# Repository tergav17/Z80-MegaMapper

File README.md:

# Z80 MegaMapper

The Z80 MegaMapper (ZMM) is designed to enhance the ability of existing retro computers. This is done by interposing the Z80 CPU and intercepting certain signals. The current version of the MegaMapper provides the following enhancements:

- An additional 512 KB of static RAM, expandable up to 2 MB.
- Simple memory management, allowing the 4 independently selectable memory banks. Banks can also be write protected.
- Virtual machine mode, supporting “transparent” traps that do not depend on a specific stack pointer location.
- Fully programmable I/O space in virtual mode, allowing device addresses to be translated between the virtual and physical address space.
- I/O trap vector allowing any I/O instruction to be emulated by software if needed.
- Software controllable interrupts, allowing the maskable interrupt to be fully controlled by the real mode hypervisor.

The expanded memory is fairly self explanatory, but the other features may require a bit of explanation. The goal of the MegaMapper is to allow a Z80 machine to support “virtual machines”. These machines, with the help of a software hypervisor, can be made to seamlessly run software from other computer architectures. A single machine can act as an MSX, Colecovision, SG-1000, ZX81, Heathkit H8, TRS-80 Model II, TI-83, etc… simply by changing what hypervisor software is running. Additionally, virtual machines can be debugged in real time, to the point of being single-steppable. 

This is different from emulation as fundamentally everything is still executing on bare hardware. It provides vast software compatibility while still scratching the “retro hardware” itch that makes emulators simply not as fun (personally). In theory, this same type of device could have been built in the 80s with off-the-shelf components. All of the heavy lifting is still done by the ~3.5 Mhz Z80 processor.

Admittedly, emulation can always provide better results than a janky virtualization set up like this. This is more of a “Because I Can” project than anything else. 

# Virtual Machine Status

## SG-1000

The important parts of this seem to work. The PSG -> AY translation is passable, but it still needs some work in terms of tone and support for the noise channel. Pausing is also buggy due to lack of functional NMI.

## MSX 1

Boots to MSX basic just fine. Can also run all of the 32K cartridge ROMs I threw at it. Keyboard matrix still needs to be updated to support all keys.

# Current Issues

The Z80 data bus buffer currently doesn't work properly due to IM2-related shenanigans. The system works fine without it, so it may be omitted in a future revision.

At the moment, there is no way to maintain IFF2 contents during a trap. This is fine for systems that don't need an NMI, but can cause interrupt issues to those that do. It should be possible to add a status bit that keeps trick of if IFF1 and IFF2 are supposed to be equal, and work backwards from there.

The classic NMOS CPUs seem to have issues sometimes with detecting clock edges on the M1 cycle. Currently, this is circumvented by just getting a faster CMOS Z80.

# Installation

The ZMM is designed to slot directly into where the Z80 plugs into the mainboard of the host computer. Everything runs on +5V, so no additional jumpers are needed.

# Limitations

One of the major design limitations of the ZMM is the fact that no provisions have been made for memory mapped I/O. Video RAM can crudely be accomplished by periodically scanning parts of memory and updating the VDP accordingly. This is very inefficient, especially the bigger the VRAM section gets. The size of the bankable sections is also limited to 16 KB, anything smaller will have to be emulated by manually copying sections of memory.

# BOM

| Quantity | Reference  | Part          | Link |
| -------- | ---------- | ------------- | ---- |
|        1 | U2         | 74LS32        |      |
|        2 | U3, U4     | 74LS670       |      |
|        1 | U5         | HM6116        |      |
|        3 | U6..8      | 74LS157       |      |
|        1 | U9         | 74LS244       |      |
|        2 | U10, U11   | 74LS374       |      |
|        1 | U12        | 74LS85        |      |
|        1 | U13        | XC9536PC44    |      |
|        1 | U14        | 74LS139       |      |
|      1-4 | U15..18    | AS6C4008      |      |
|        0 | U19        | 74LS245       |      |
|       19 | C1..19     | 0.1 uF C      |      |
|        1 | C20        | 100 uF        |      |

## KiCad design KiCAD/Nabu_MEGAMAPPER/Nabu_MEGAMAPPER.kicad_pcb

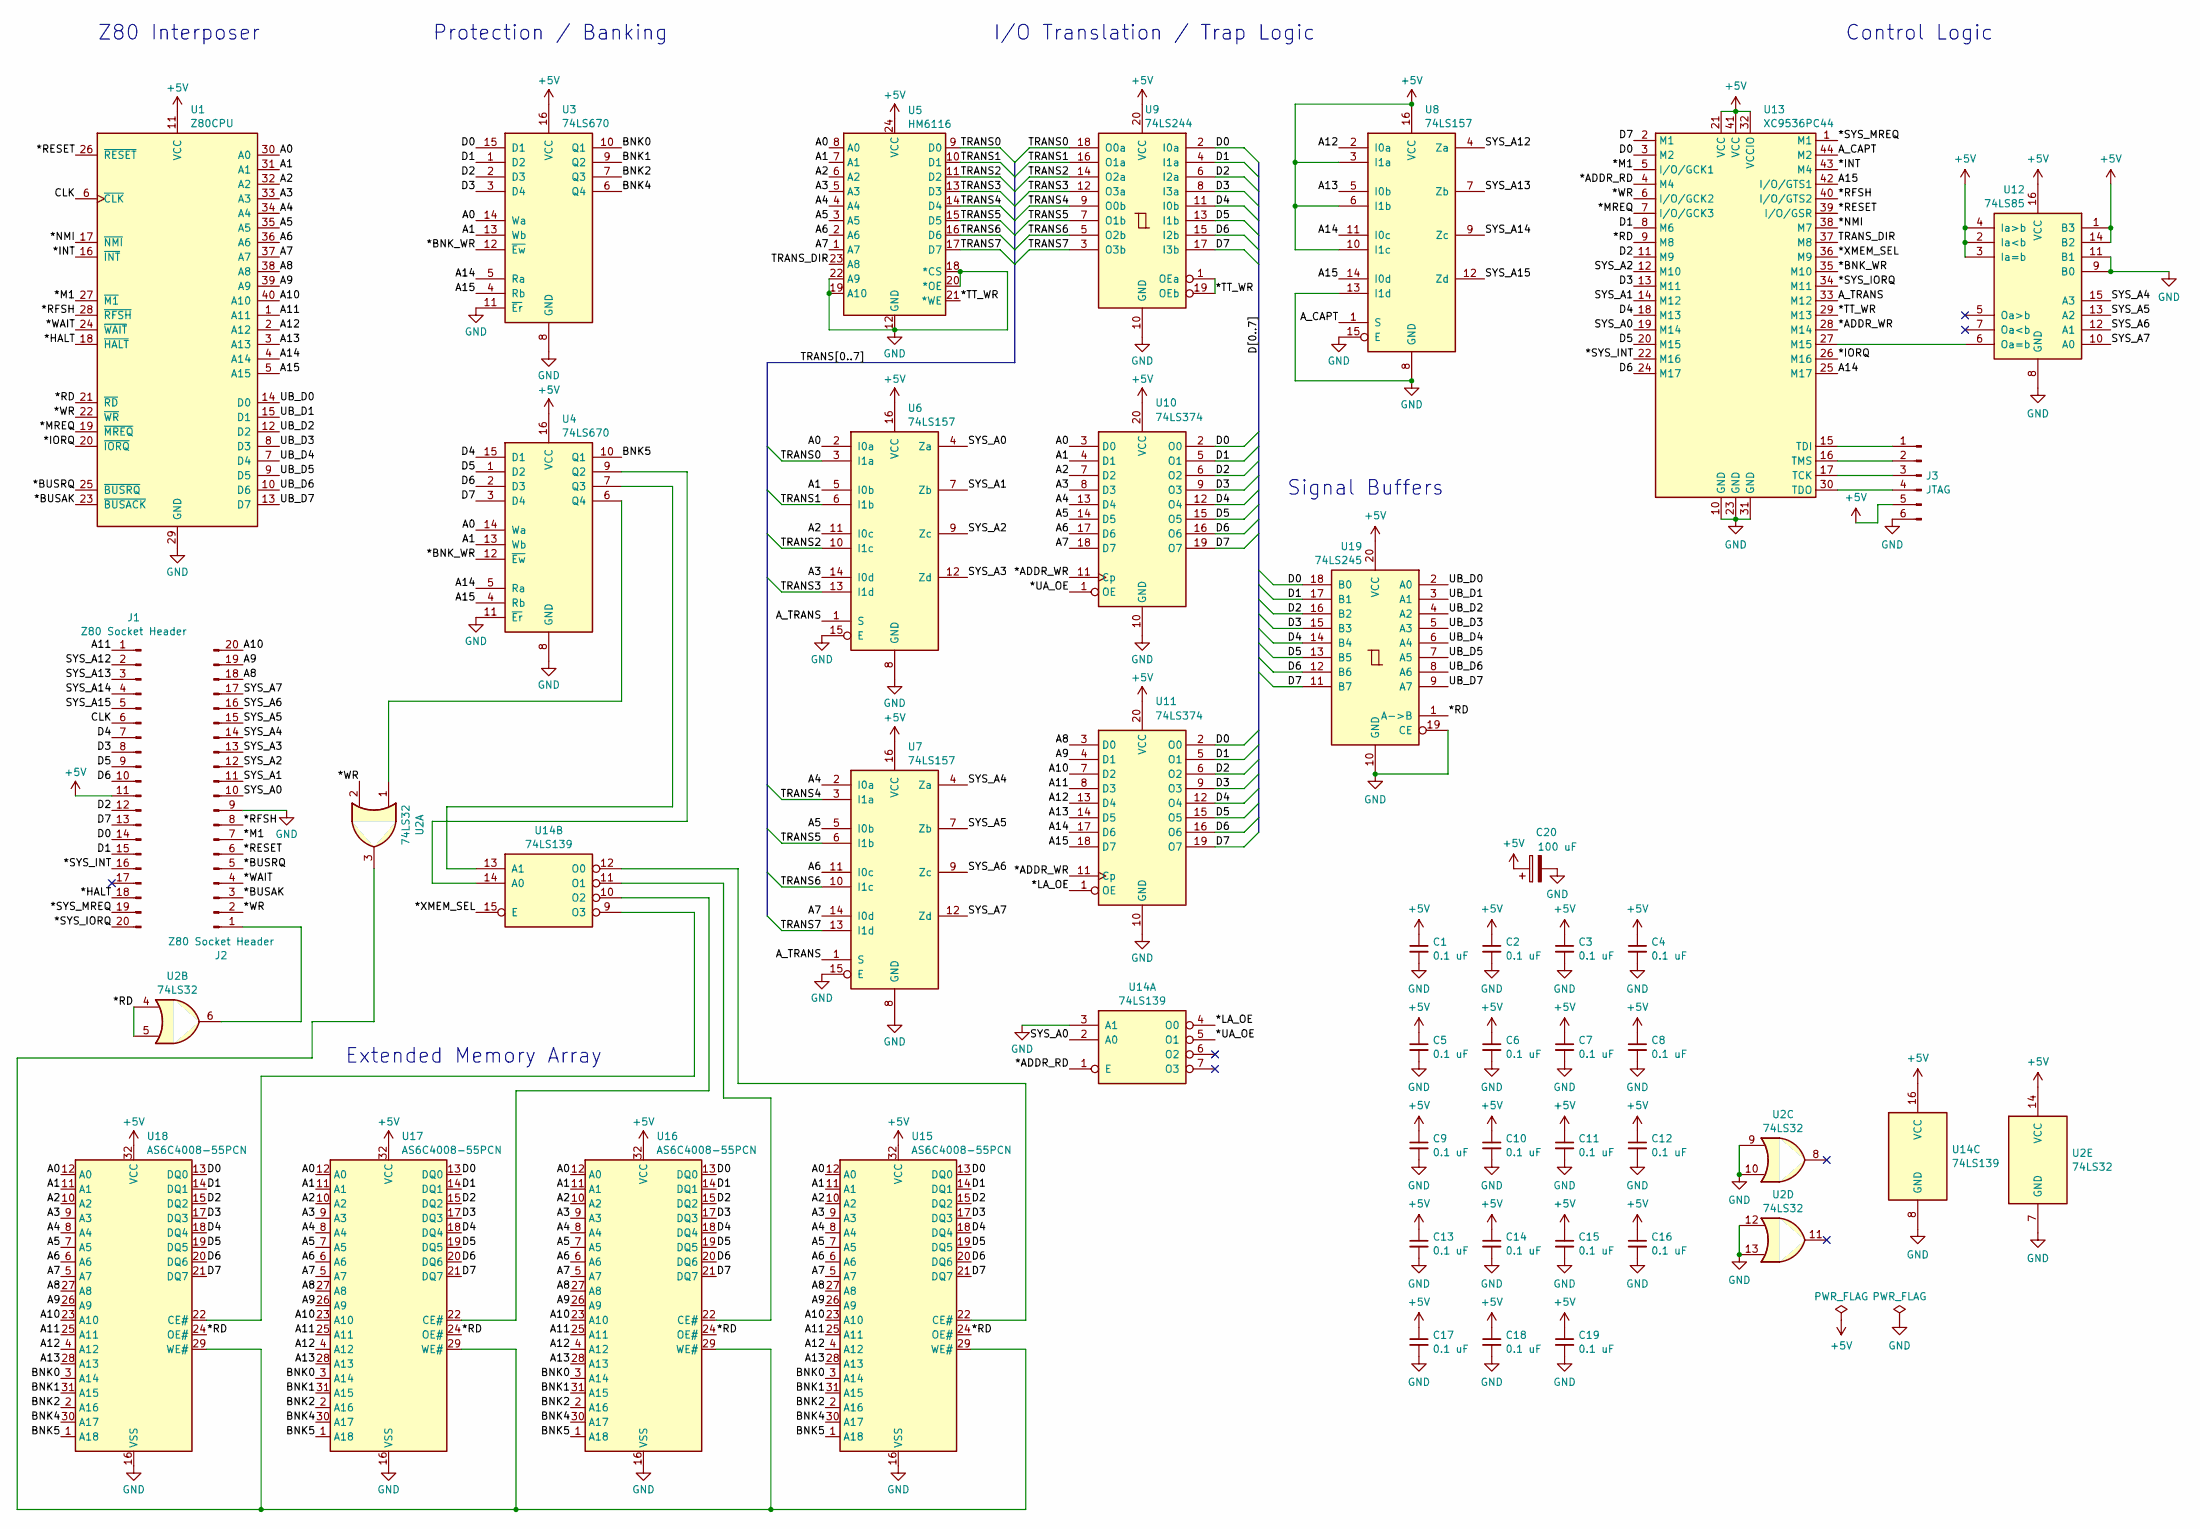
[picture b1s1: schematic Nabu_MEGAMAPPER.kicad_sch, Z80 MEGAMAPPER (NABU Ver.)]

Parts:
C1, C2, C3, C4, C5, C6, C7, C8, C9, C10, C11, C12, C13, C14, C15, C16, C17, C18, C19: 0.1 uF; C_Disc_D5.0mm_W2.5mm_P5.00mm
C20: 100 uF; CP_Radial_D6.3mm_P2.50mm
J1, J2: Z80 Socket Header; PinHeader_1x20_P2.54mm_Vertical
J3: JTAG; PinHeader_1x06_P2.54mm_Vertical
U1: Z80CPU; DIP-40_W15.24mm
U2: 74LS32; DIP-14_W7.62mm
U3, U4: 74LS670; DIP-16_W7.62mm
U5: HM6116; DIP-24_W15.24mm
U6, U7, U8: 74LS157; DIP-16_W7.62mm
U9: 74LS244; DIP-20_W7.62mm
U10, U11: 74LS374; DIP-20_W7.62mm
U12: 74LS85; DIP-16_W7.62mm
U13: XC9536PC44; PLCC-44_THT-Socket
U14: 74LS139; DIP-16_W7.62mm
U15, U16, U17, U18: AS6C4008-55PCN; DIP-32_W15.24mm
U19: 74LS245; DIP-20_W7.62mm

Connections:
+5V: C1.1, C2.1, C3.1, C4.1, C5.1, C6.1, C7.1, C8.1, C9.1, C10.1, C11.1, C12.1, C13.1, C14.1, C15.1, C16.1, C17.1, C18.1, C19.1, C20.1, J1.11, J3.5, U1.11 (VCC), U2.14 (VCC), U3.16 (VCC), U4.16 (VCC), U5.24 (VCC), U6.16 (VCC), U7.16 (VCC), U8.3 (I1a), U8.6 (I1b), U8.10 (I1c), U8.16 (VCC), U9.20 (VCC), U10.20 (VCC), U11.20 (VCC), U12.1 (B3), U12.2 (Ia<b), U12.3 (Ia=b), U12.4 (Ia>b), U12.14 (B2), U12.16 (VCC), U13.21 (VCC), U13.32 (VCCIO), U13.41 (VCC), U14.16 (VCC), U15.32 (VCC), U16.32 (VCC), U17.32 (VCC), U18.32 (VCC), U19.20 (VCC)
/*ADDR_RD: U13.4 (M4), U14.1 (E)
/*ADDR_WR: U10.11 (Cp), U11.11 (Cp), U13.28 (M14)
/*BNK_WR: U3.12 (~Ew), U4.12 (~Ew), U13.35 (M10)
/*BUSAK: J2.3, U1.23 (~BUSACK)
/*BUSRQ: J2.5, U1.25 (~BUSRQ)
/*HALT: J1.18, U1.18 (~HALT)
/*INT: U1.16 (~INT), U13.43 (M4)
/*IORQ: U1.20 (~IORQ), U13.26 (M16)
/*LA_OE: U11.1 (OE), U14.4 (O0)
/*M1: J2.7, U1.27 (~M1), U13.5 (I/O/GCK1)
/*MREQ: U1.19 (~MREQ), U13.7 (I/O/GCK3)
/*NMI: U1.17 (~NMI), U13.38 (M7)
/*RD: U1.21 (~RD), U2.4, U2.5, U13.9 (M8), U15.24 (OE#), U16.24 (OE#), U17.24 (OE#), U18.24 (OE#), U19.1 (A->B)
/*RESET: J2.6, U1.26 (~RESET), U13.39 (I/O/GSR)
/*RFSH: J2.8, U1.28 (~RFSH), U13.40 (I/O/GTS2)
/*SYS_INT: J1.16, U13.22 (M16)
/*SYS_IORQ: J1.20, U13.34 (M11)
/*SYS_MREQ: J1.19, U13.1 (M1)
/*TT_WR: U5.21 (*WE), U9.1 (OEa), U9.19 (OEb), U13.29 (M13)
/*UA_OE: U10.1 (OE), U14.5 (O1)
/*WAIT: J2.4, U1.24 (~WAIT)
/*WR: J2.2, U1.22 (~WR), U2.2, U13.6 (I/O/GCK2)
/*XMEM_SEL: U13.36 (M9), U14.15 (E)
/A0: U1.30 (A0), U3.14 (Wa), U4.14 (Wa), U5.8 (A0), U6.2 (I0a), U10.3 (D0), U15.12 (A0), U16.12 (A0), U17.12 (A0), U18.12 (A0)
/A1: U1.31 (A1), U3.13 (Wb), U4.13 (Wb), U5.7 (A1), U6.5 (I0b), U10.4 (D1), U15.11 (A1), U16.11 (A1), U17.11 (A1), U18.11 (A1)
/A2: U1.32 (A2), U5.6 (A2), U6.11 (I0c), U10.7 (D2), U15.10 (A2), U16.10 (A2), U17.10 (A2), U18.10 (A2)
/A3: U1.33 (A3), U5.5 (A3), U6.14 (I0d), U10.8 (D3), U15.9 (A3), U16.9 (A3), U17.9 (A3), U18.9 (A3)
/A4: U1.34 (A4), U5.4 (A4), U7.2 (I0a), U10.13 (D4), U15.8 (A4), U16.8 (A4), U17.8 (A4), U18.8 (A4)
/A5: U1.35 (A5), U5.3 (A5), U7.5 (I0b), U10.14 (D5), U15.7 (A5), U16.7 (A5), U17.7 (A5), U18.7 (A5)
/A6: U1.36 (A6), U5.2 (A6), U7.11 (I0c), U10.17 (D6), U15.6 (A6), U16.6 (A6), U17.6 (A6), U18.6 (A6)
/A7: U1.37 (A7), U5.1 (A7), U7.14 (I0d), U10.18 (D7), U15.5 (A7), U16.5 (A7), U17.5 (A7), U18.5 (A7)
/A8: J2.18, U1.38 (A8), U11.3 (D0), U15.27 (A8), U16.27 (A8), U17.27 (A8), U18.27 (A8)
/A9: J2.19, U1.39 (A9), U11.4 (D1), U15.26 (A9), U16.26 (A9), U17.26 (A9), U18.26 (A9)
/A10: J2.20, U1.40 (A10), U11.7 (D2), U15.23 (A10), U16.23 (A10), U17.23 (A10), U18.23 (A10)
/A11: J1.1, U1.1 (A11), U11.8 (D3), U15.25 (A11), U16.25 (A11), U17.25 (A11), U18.25 (A11)
/A12: U1.2 (A12), U8.2 (I0a), U11.13 (D4), U15.4 (A12), U16.4 (A12), U17.4 (A12), U18.4 (A12)
/A13: U1.3 (A13), U8.5 (I0b), U11.14 (D5), U15.28 (A13), U16.28 (A13), U17.28 (A13), U18.28 (A13)
/A14: U1.4 (A14), U3.5 (Ra), U4.5 (Ra), U8.11 (I0c), U11.17 (D6), U13.25 (M17)
/A15: U1.5 (A15), U3.4 (Rb), U4.4 (Rb), U8.14 (I0d), U11.18 (D7), U13.42 (I/O/GTS1)
/A_CAPT: U8.1 (S), U13.44 (M2)
/A_TRANS: U6.1 (S), U7.1 (S), U13.33 (M12)
/BNK0: U3.10 (Q1), U15.3 (A14), U16.3 (A14), U17.3 (A14), U18.3 (A14)
/BNK1: U3.9 (Q2), U15.31 (A15), U16.31 (A15), U17.31 (A15), U18.31 (A15)
/BNK2: U3.7 (Q3), U15.2 (A16), U16.2 (A16), U17.2 (A16), U18.2 (A16)
/BNK4: U3.6 (Q4), U15.30 (A17), U16.30 (A17), U17.30 (A17), U18.30 (A17)
/BNK5: U4.10 (Q1), U15.1 (A18), U16.1 (A18), U17.1 (A18), U18.1 (A18)
/CLK: J1.6, U1.6 (~CLK)
/D0: J1.14, U3.15 (D1), U9.2 (I0a), U10.2 (O0), U11.2 (O0), U13.3 (M2), U15.13 (DQ0), U16.13 (DQ0), U17.13 (DQ0), U18.13 (DQ0), U19.18 (B0)
/D1: J1.15, U3.1 (D2), U9.4 (I1a), U10.5 (O1), U11.5 (O1), U13.8 (M6), U15.14 (DQ1), U16.14 (DQ1), U17.14 (DQ1), U18.14 (DQ1), U19.17 (B1)
/D2: J1.12, U3.2 (D3), U9.6 (I2a), U10.6 (O2), U11.6 (O2), U13.11 (M9), U15.15 (DQ2), U16.15 (DQ2), U17.15 (DQ2), U18.15 (DQ2), U19.16 (B2)
/D3: J1.8, U3.3 (D4), U9.8 (I3a), U10.9 (O3), U11.9 (O3), U13.13 (M11), U15.17 (DQ3), U16.17 (DQ3), U17.17 (DQ3), U18.17 (DQ3), U19.15 (B3)
/D4: J1.7, U4.15 (D1), U9.11 (I0b), U10.12 (O4), U11.12 (O4), U13.18 (M13), U15.18 (DQ4), U16.18 (DQ4), U17.18 (DQ4), U18.18 (DQ4), U19.14 (B4)
/D5: J1.9, U4.1 (D2), U9.13 (I1b), U10.15 (O5), U11.15 (O5), U13.20 (M15), U15.19 (DQ5), U16.19 (DQ5), U17.19 (DQ5), U18.19 (DQ5), U19.13 (B5)
/D6: J1.10, U4.2 (D3), U9.15 (I2b), U10.16 (O6), U11.16 (O6), U13.24 (M17), U15.20 (DQ6), U16.20 (DQ6), U17.20 (DQ6), U18.20 (DQ6), U19.12 (B6)
/D7: J1.13, U4.3 (D4), U9.17 (I3b), U10.19 (O7), U11.19 (O7), U13.2 (M1), U15.21 (DQ7), U16.21 (DQ7), U17.21 (DQ7), U18.21 (DQ7), U19.11 (B7)
/SYS_A0: J2.10, U6.4 (Za), U13.19 (M14), U14.2 (A0)
/SYS_A1: J2.11, U6.7 (Zb), U13.14 (M12)
/SYS_A2: J2.12, U6.9 (Zc), U13.12 (M10)
/SYS_A3: J2.13, U6.12 (Zd)
/SYS_A4: J2.14, U7.4 (Za), U12.15 (A3)
/SYS_A5: J2.15, U7.7 (Zb), U12.13 (A2)
/SYS_A6: J2.16, U7.9 (Zc), U12.12 (A1)
/SYS_A7: J2.17, U7.12 (Zd), U12.10 (A0)
/SYS_A12: J1.2, U8.4 (Za)
/SYS_A13: J1.3, U8.7 (Zb)
/SYS_A14: J1.4, U8.9 (Zc)
/SYS_A15: J1.5, U8.12 (Zd)
/TRANS0: U5.9 (D0), U6.3 (I1a), U9.18 (O0a)
/TRANS1: U5.10 (D1), U6.6 (I1b), U9.16 (O1a)
/TRANS2: U5.11 (D2), U6.10 (I1c), U9.14 (O2a)
/TRANS3: U5.13 (D3), U6.13 (I1d), U9.12 (O3a)
/TRANS4: U5.14 (D4), U7.3 (I1a), U9.9 (O0b)
/TRANS5: U5.15 (D5), U7.6 (I1b), U9.7 (O1b)
/TRANS6: U5.16 (D6), U7.10 (I1c), U9.5 (O2b)
/TRANS7: U5.17 (D7), U7.13 (I1d), U9.3 (O3b)
/TRANS_DIR: U5.23 (A8), U13.37 (M8)
/UB_D0: U1.14 (D0), U19.2 (A0)
/UB_D1: U1.15 (D1), U19.3 (A1)
/UB_D2: U1.12 (D2), U19.4 (A2)
/UB_D3: U1.8 (D3), U19.5 (A3)
/UB_D4: U1.7 (D4), U19.6 (A4)
/UB_D5: U1.9 (D5), U19.7 (A5)
/UB_D6: U1.10 (D6), U19.8 (A6)
/UB_D7: U1.13 (D7), U19.9 (A7)
GND: C1.2, C2.2, C3.2, C4.2, C5.2, C6.2, C7.2, C8.2, C9.2, C10.2, C11.2, C12.2, C13.2, C14.2, C15.2, C16.2, C17.2, C18.2, C19.2, C20.2, J2.9, J3.6, U1.29 (GND), U2.7 (GND), U2.9, U2.10, U2.12, U2.13, U3.8 (GND), U3.11 (~Er), U4.8 (GND), U4.11 (~Er), U5.12 (GND), U5.18 (*CS), U5.19 (A10), U5.20 (*OE), U5.22 (A9), U6.8 (GND), U6.15 (E), U7.8 (GND), U7.15 (E), U8.8 (GND), U8.13 (I1d), U8.15 (E), U9.10 (GND), U10.10 (GND), U11.10 (GND), U12.8 (GND), U12.9 (B0), U12.11 (B1), U13.10 (GND), U13.23 (GND), U13.31 (GND), U14.3 (A1), U14.8 (GND), U15.16 (VSS), U16.16 (VSS), U17.16 (VSS), U18.16 (VSS), U19.10 (GND), U19.19 (CE)
unnamed: J2.1, U2.6
unnamed: J3.1, U13.15 (TDI)
unnamed: J3.2, U13.16 (TMS)
unnamed: J3.3, U13.17 (TCK)
unnamed: J3.4, U13.30 (TDO)
unnamed: U2.1, U4.6 (Q4)
unnamed: U12.6 (Oa=b), U13.27 (M15)
unnamed: U4.9 (Q2), U14.14 (A0)
unnamed: U4.7 (Q3), U14.13 (A1)
unnamed: U14.12 (O0), U15.22 (CE#)
unnamed: U14.11 (O1), U16.22 (CE#)
unnamed: U14.10 (O2), U17.22 (CE#)
unnamed: U14.9 (O3), U18.22 (CE#)
unnamed: U2.3, U15.29 (WE#), U16.29 (WE#), U17.29 (WE#), U18.29 (WE#)

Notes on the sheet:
Protection / Banking
Z80 Interposer
Extended Memory Array
Control Logic
I/O Translation / Trap Logic
Signal Buffers

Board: 2 copper layers, 42 parts (0 on the bottom side), 100 nets, no tracks yet.

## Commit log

2024-05-10 Inital commit
2024-05-11 Removed some of the 22V10s in favor of a CPLD
2024-05-14 Continued work on schematic
2024-05-16 Started on CPLD verilog design
2024-05-17 Continued work on CPLD verilog
2024-05-18 Integrated register module with top level assembly
2024-05-19 Worked on the opcode detection verilog
2024-05-20 Added RETN tracking to opcode logic
2024-05-21 Continued work on state logic
2024-05-22 Added theory of operation file
2024-05-23 Updated theory of operation
2024-05-24 Continued work on theory of operation
2024-05-25 Added memory map
2024-05-26 Continued work on modes logic
2024-05-27 Fleshed out mode logic a little
2024-05-28 Updated theory doc
2024-05-29 Updated how address decoding works
2024-05-30 Added full address capture logic to schematic
2024-05-31 Started converting mode verilog to new logic
2024-06-01 Continued work on mode logic
2024-06-02 Updated theory document
2024-06-02 Respecced how page protection will work
2024-06-04 Cotinued mode stuff
2024-06-05 Finally got modes logic into a somewhat sane state
2024-06-06 Work on memory override logic
2024-06-07 Added activation signals for address and bank registers
2024-06-08 Finished first version of complete MMU control code
2024-06-09 Started laying out MegaMapper PCB
2024-06-10 Continued work on PCB layout
2024-06-11 Added bulk storage capacitor and started designing layout
2024-06-12 Redid board layout for better routing
2024-06-13 Added routing and gerbers
2024-06-14 Updated theory doc to latest spec
2024-06-18 Added assembly.ucf file
2024-06-20 Added JED file
2024-07-08 Added toolchain stuff for writing test programs
2024-07-09 Started work on ZMM basic test
2024-07-10 Continued work on ZMM basic test program
2024-07-11 Switched untrap logic to use RETN
2024-07-11 Updated final assembly JED file
2024-07-13 Added images of finished boards
2024-07-16 Continued work on ZMM test
2024-07-17 Continued work on ZMM basic test
2024-07-18 Continued work on basic tests
2024-07-19 Started work on memory integrity test
2024-07-20 Continued work on memory integrity test
2024-07-20 Build script work
2024-07-20 Debugging work on TPAINTEG
2024-07-22 Started work on IDEINTEG
2024-07-23 Added base IDE code to IDEINTEG
2024-07-24 Continued work in IDEINTEG
2024-07-25 Continued work on IDEINTEG
2024-07-27 Removed testing stubs
2024-07-27 Started work on ZMM memory test
2024-07-28 Added dummy CPLD file
2024-07-28 Modified assembly to pass some signals directly through
2024-07-28 V2 of test assembly
2024-07-29 V3 of test assembly
2024-07-29 V4 version of test assembly
2024-07-29 V5 version of test assembly
2024-07-29 Fixed issue with IORQ interposer making IM2 sad :(
2024-07-29 Page test in ZMMBAS
2024-08-08 ZMM trap engagement test
2024-08-09 Fixed test #4
2024-08-09 Fixed timing issue for I/O violations
2024-08-10 Trap full overlay test + new ctrl layout
2024-08-10 Update ctrl register layout + HW intercept mode
2024-08-11 Test trap state recovery
2024-08-11 Started work on KRISYS
2024-08-11 KRISYS memory checking
2024-08-12 Memory management code
2024-08-13 Continued resource loaer stuff
2024-08-14 Continued work on resource loading
2024-08-14 File open logic
2024-08-15 Resource file parsing work
2024-08-16 Finish res_load routine
2024-08-16 Re-enabled init calls
2024-08-16 Fixed bug with res_load
2024-08-16 Trap management work
2024-08-18 Standard I/O instructions handled
2024-08-18 Inital version of I/O trap handler
2024-08-19 Test version of KSG1000
2024-08-19 Debugging work on KSG1000
2024-08-19 VDP hello test program
2024-08-20 Continued debugging work
2024-08-21 Fixed irq bug and changed registers to unblocked
2024-08-22 Start work on debugger
2024-08-23 Continued work on debugger
2024-08-26 Debugging slog
2024-08-26 Who loves debugging? (we do! we do!)
2024-08-27 More debuggin
2024-08-28 Minor update to CPLD
2024-08-29 Fixed annoying stack capture bug, more trap sadness
2024-08-30 Unbreak test 6
2024-08-31 Started work on interrupt interception
2024-08-31 More debugging and fixed IY bug
2024-09-01 Updated debugger and reverted CPLD bodge
2024-09-01 Updated VM to use virtual interrupts instead of passthru
2024-09-01 Testing a verilog bodge
2024-09-01 Reverse bodge
2024-09-01 Added constraint on m1 signal
2024-09-01 Minor refactor of capture logic
2024-09-01 Updating state while reading is now BANNED
2024-09-02 IOTEST for testing I/O traps
2024-09-02 Fixed IX/IY BIT state machine bug
2024-09-03 Added logic to keep IRQ responses from trigger traps
2024-09-03 Implementation fix
2024-09-04 Inital version of SN76489 driver
2024-09-04 Frequencies are correct, but volume is wack
2024-09-05 NMI response work started
2024-09-06 Started work on MSX 1 core
2024-09-06 Update MSX core and debugger
2024-09-07 First version of MSX core working
2024-09-08 MSX core keyboard driver update
2024-09-08 Joystick support on MSX 1
2024-09-12 Remove bodge from modes logic
2024-09-16 Started working on colecovision core again
2024-09-18 Added tracking for misc instructions
2024-09-24 Started work on block device interace
2024-09-25 Function prototypes for block devices
2024-09-26 Set up boilerplate for KFUZIX core
2024-09-27 Fixed build script
2024-09-28 KFUZIX console out
2024-09-29 Incremental work on I/O subsystem
